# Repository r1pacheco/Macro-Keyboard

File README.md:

# Macro-Keyboard
Making a macro keyboard to increase efficiency in daily tasks and CAD/Programming hotkeys. 
Utilizes the *Black Pill V2.0* controller from *WeAct Studios* (STM32F411CEU6 package) controlled by the Arduino IDE.

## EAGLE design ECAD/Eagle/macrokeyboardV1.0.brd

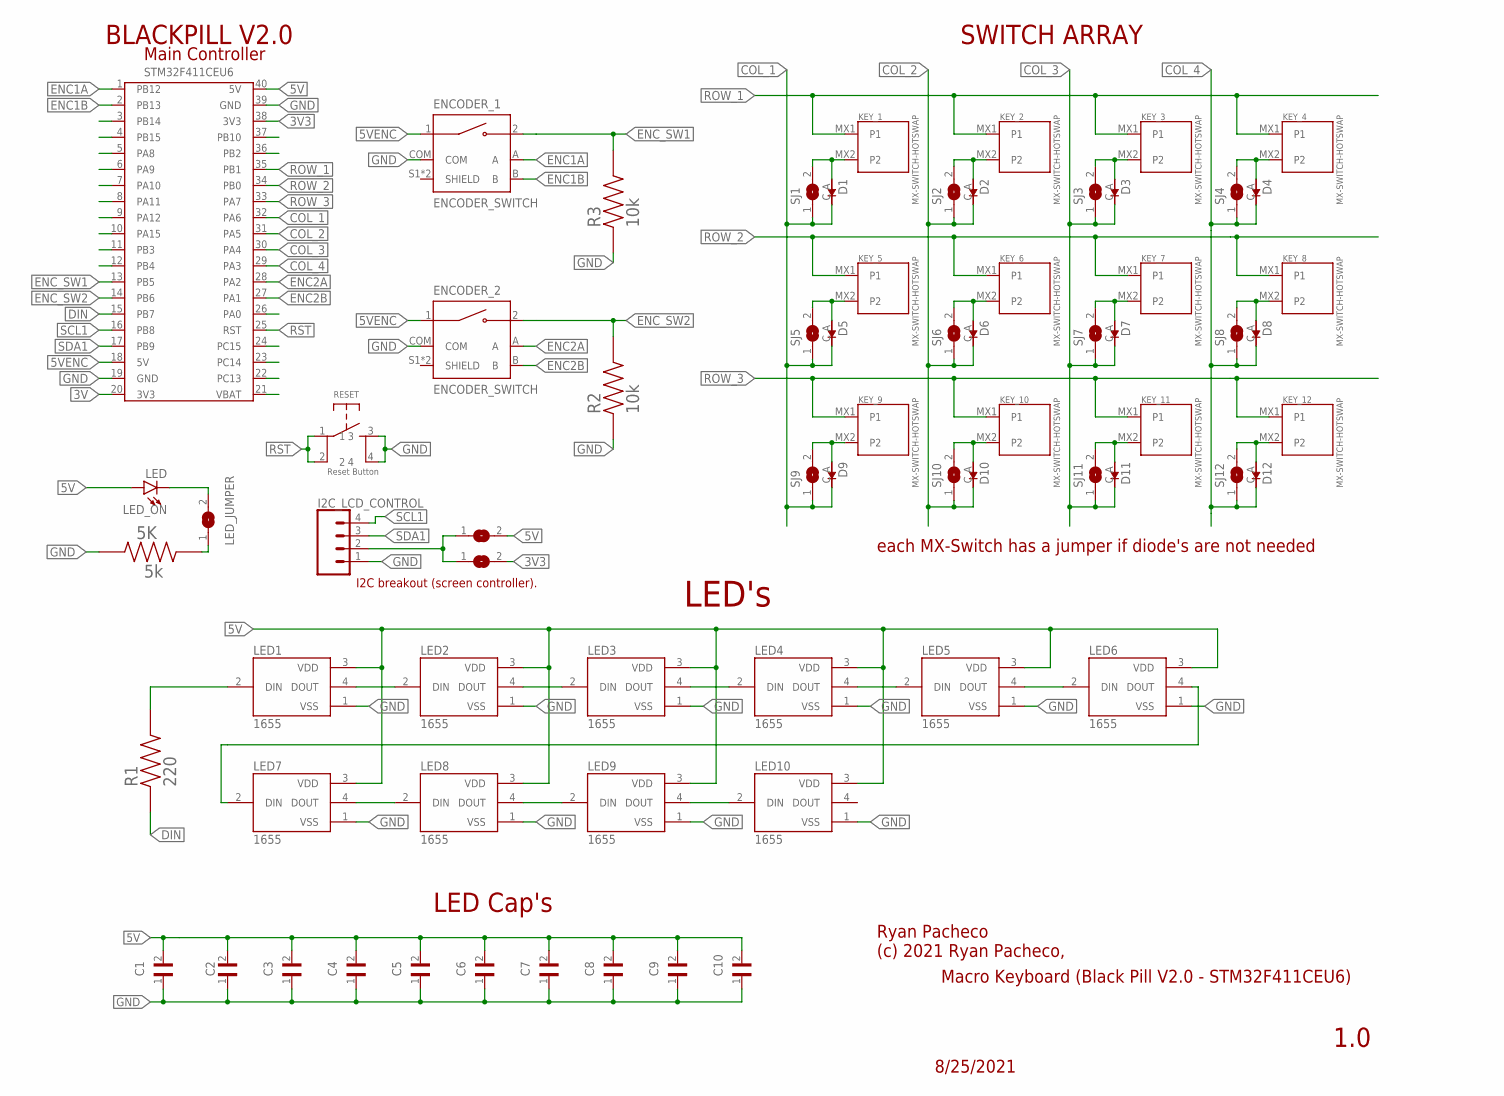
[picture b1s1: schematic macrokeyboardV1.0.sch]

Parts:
3.3V_I2C, 5V_I2C: SJ
5K: 5k; RESC3216X70N
C1: 100n; CAPC3216X88N
C2, C3, C4, C5, C7, C8, C9: C1206C104K5RAC7210; CAPC3216X88N
C6, C10: 100nF; CAPC3216X88N
D1, D2, D3, D4, D5, D6, D7, D8, D9, D10, D11, D12: 1N4148W-7-F; SOD3715X135N
ENCODER_1, ENCODER_2: ENCODER_SWITCH; XDCR_PEC11R-4215F-S0024
I2C_LCD_CONTROL: CONN_04; 1X04
KEY_1, KEY_2, KEY_3, KEY_4, KEY_5, KEY_6, KEY_7, KEY_8, KEY_9, KEY_10, KEY_11, KEY_12: MX-SWITCH-HOTSWAP; MXHSPCB-1U
LED1, LED2, LED3, LED4, LED5, LED6, LED7, LED8, LED9, LED10: 1655; LED_1655
LED_JUMPER: SJ
LED_ON: LED; LED-1206
R1: 220; RESC3216X70N
R2, R3: 10k; RESC3216X70N
RESET: Reset Button; PUSHBUTTON
SJ1, SJ2, SJ3, SJ4, SJ5, SJ6, SJ7, SJ8, SJ9, SJ10, SJ11, SJ12: SJ
U$2: STM32F411CEU6; BLACKPILL_V2

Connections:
3V: U$2.20 (3V3)
3V3: 3.3V_I2C.2, U$2.38 (3V3)
5V: 5V_I2C.2, C1.2, C2.2, C3.2, C4.2, C5.2, C6.2, C7.2, C8.2, C9.2, C10.2, LED1.3 (VDD), LED2.3 (VDD), LED3.3 (VDD), LED4.3 (VDD), LED5.3 (VDD), LED6.3 (VDD), LED7.3 (VDD), LED8.3 (VDD), LED9.3 (VDD), LED10.3 (VDD), LED_ON.A, U$2.40 (5V)
5VENC: ENCODER_1.1, ENCODER_2.1, U$2.18 (5V)
COL_1: D1.C (K), D5.C (K), D9.C (K), SJ1.1, SJ5.1, SJ9.1, U$2.32 (PA6)
COL_2: D2.C (K), D6.C (K), D10.C (K), SJ2.1, SJ6.1, SJ10.1, U$2.31 (PA5)
COL_3: D3.C (K), D7.C (K), D11.C (K), SJ3.1, SJ7.1, SJ11.1, U$2.30 (PA4)
COL_4: D4.C (K), D8.C (K), D12.C (K), SJ4.1, SJ8.1, SJ12.1, U$2.29 (PA3)
DIN: R1.1, U$2.15 (PB7)
ENC1A: ENCODER_1.A, U$2.1 (PB12)
ENC1B: ENCODER_1.B, U$2.2 (PB13)
ENC2A: ENCODER_2.A, U$2.28 (PA2)
ENC2B: ENCODER_2.B, U$2.27 (PA1)
ENC_SW1: ENCODER_1.2, R3.2, U$2.13 (PB5)
ENC_SW2: ENCODER_2.2, R2.2, U$2.14 (PB6)
GND: 5K.2, C1.1, C2.1, C3.1, C4.1, C5.1, C6.1, C7.1, C8.1, C9.1, C10.1, ENCODER_1.COM, ENCODER_2.COM, I2C_LCD_CONTROL.1, LED1.1 (VSS), LED2.1 (VSS), LED3.1 (VSS), LED4.1 (VSS), LED5.1 (VSS), LED6.1 (VSS), LED7.1 (VSS), LED8.1 (VSS), LED9.1 (VSS), LED10.1 (VSS), R2.1, R3.1, RESET.3, RESET.4, U$2.19 (GND), U$2.39 (GND)
unnamed: D1.A, KEY_1.MX2 (P2), SJ1.2
unnamed: D2.A, KEY_2.MX2 (P2), SJ2.2
unnamed: D3.A, KEY_3.MX2 (P2), SJ3.2
unnamed: D4.A, KEY_4.MX2 (P2), SJ4.2
unnamed: D5.A, KEY_5.MX2 (P2), SJ5.2
unnamed: D6.A, KEY_6.MX2 (P2), SJ6.2
unnamed: D7.A, KEY_7.MX2 (P2), SJ7.2
unnamed: D8.A, KEY_8.MX2 (P2), SJ8.2
unnamed: D9.A, KEY_9.MX2 (P2), SJ9.2
unnamed: D10.A, KEY_10.MX2 (P2), SJ10.2
unnamed: D11.A, KEY_11.MX2 (P2), SJ11.2
unnamed: D12.A, KEY_12.MX2 (P2), SJ12.2
unnamed: 5K.1, LED_JUMPER.1
unnamed: LED_JUMPER.2, LED_ON.C
unnamed: LED1.2 (DIN), R1.2
unnamed: LED1.4 (DOUT), LED2.2 (DIN)
unnamed: LED2.4 (DOUT), LED3.2 (DIN)
unnamed: LED7.4 (DOUT), LED8.2 (DIN)
unnamed: LED8.4 (DOUT), LED9.2 (DIN)
unnamed: 3.3V_I2C.1, 5V_I2C.1, I2C_LCD_CONTROL.2
unnamed: LED6.4 (DOUT), LED7.2 (DIN)
unnamed: LED9.4 (DOUT), LED10.2 (DIN)
unnamed: LED5.4 (DOUT), LED6.2 (DIN)
unnamed: LED4.4 (DOUT), LED5.2 (DIN)
unnamed: LED3.4 (DOUT), LED4.2 (DIN)
ROW_1: KEY_1.MX1 (P1), KEY_2.MX1 (P1), KEY_3.MX1 (P1), KEY_4.MX1 (P1), U$2.35 (PB1)
ROW_2: KEY_5.MX1 (P1), KEY_6.MX1 (P1), KEY_7.MX1 (P1), KEY_8.MX1 (P1), U$2.34 (PB0)
ROW_3: KEY_9.MX1 (P1), KEY_10.MX1 (P1), KEY_11.MX1 (P1), KEY_12.MX1 (P1), U$2.33 (PA7)
RST: RESET.1, RESET.2, U$2.25 (RST)
SCL1: I2C_LCD_CONTROL.4, U$2.16 (PB8)
SDA1: I2C_LCD_CONTROL.3, U$2.17 (PB9)

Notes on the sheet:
1.0
Macro Keyboard (Black Pill V2.0 - STM32F411CEU6)
8/25/2021
Ryan Pacheco (c) 2021 Ryan Pacheco,
SWITCH ARRAY
BLACKPILL V2.0
Main Controller
LED's
LED Cap's
each MX-Switch has a jumper if diode's are not needed
I2C breakout (screen controller).

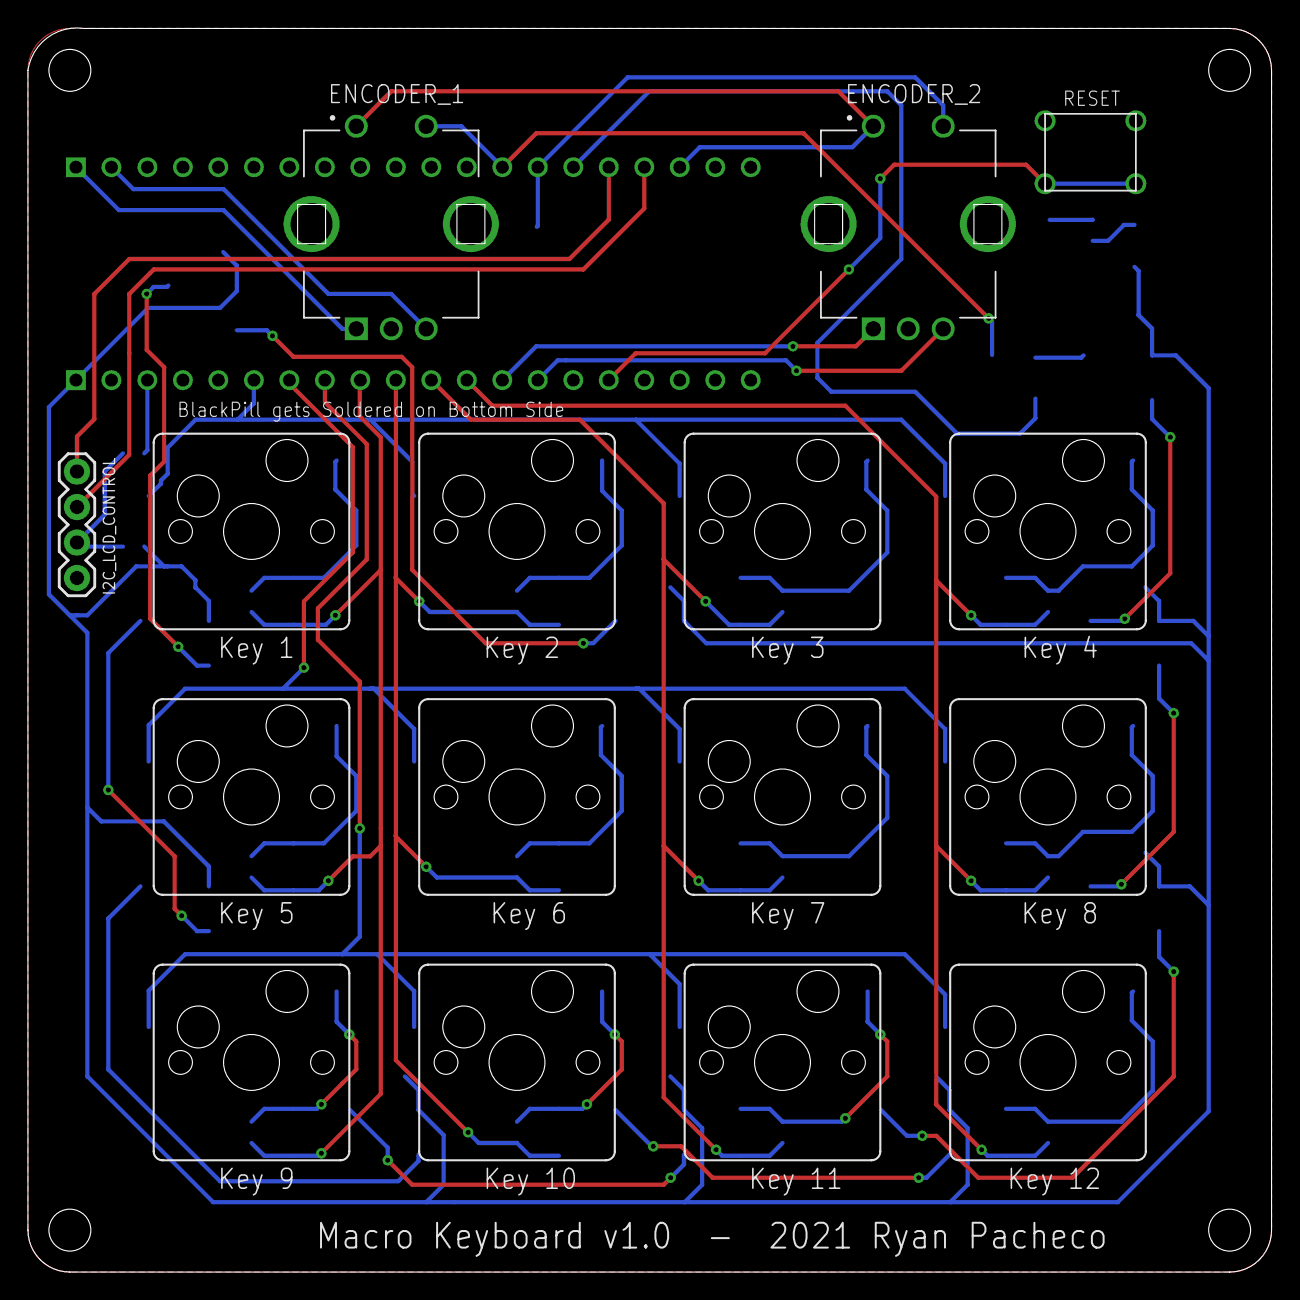
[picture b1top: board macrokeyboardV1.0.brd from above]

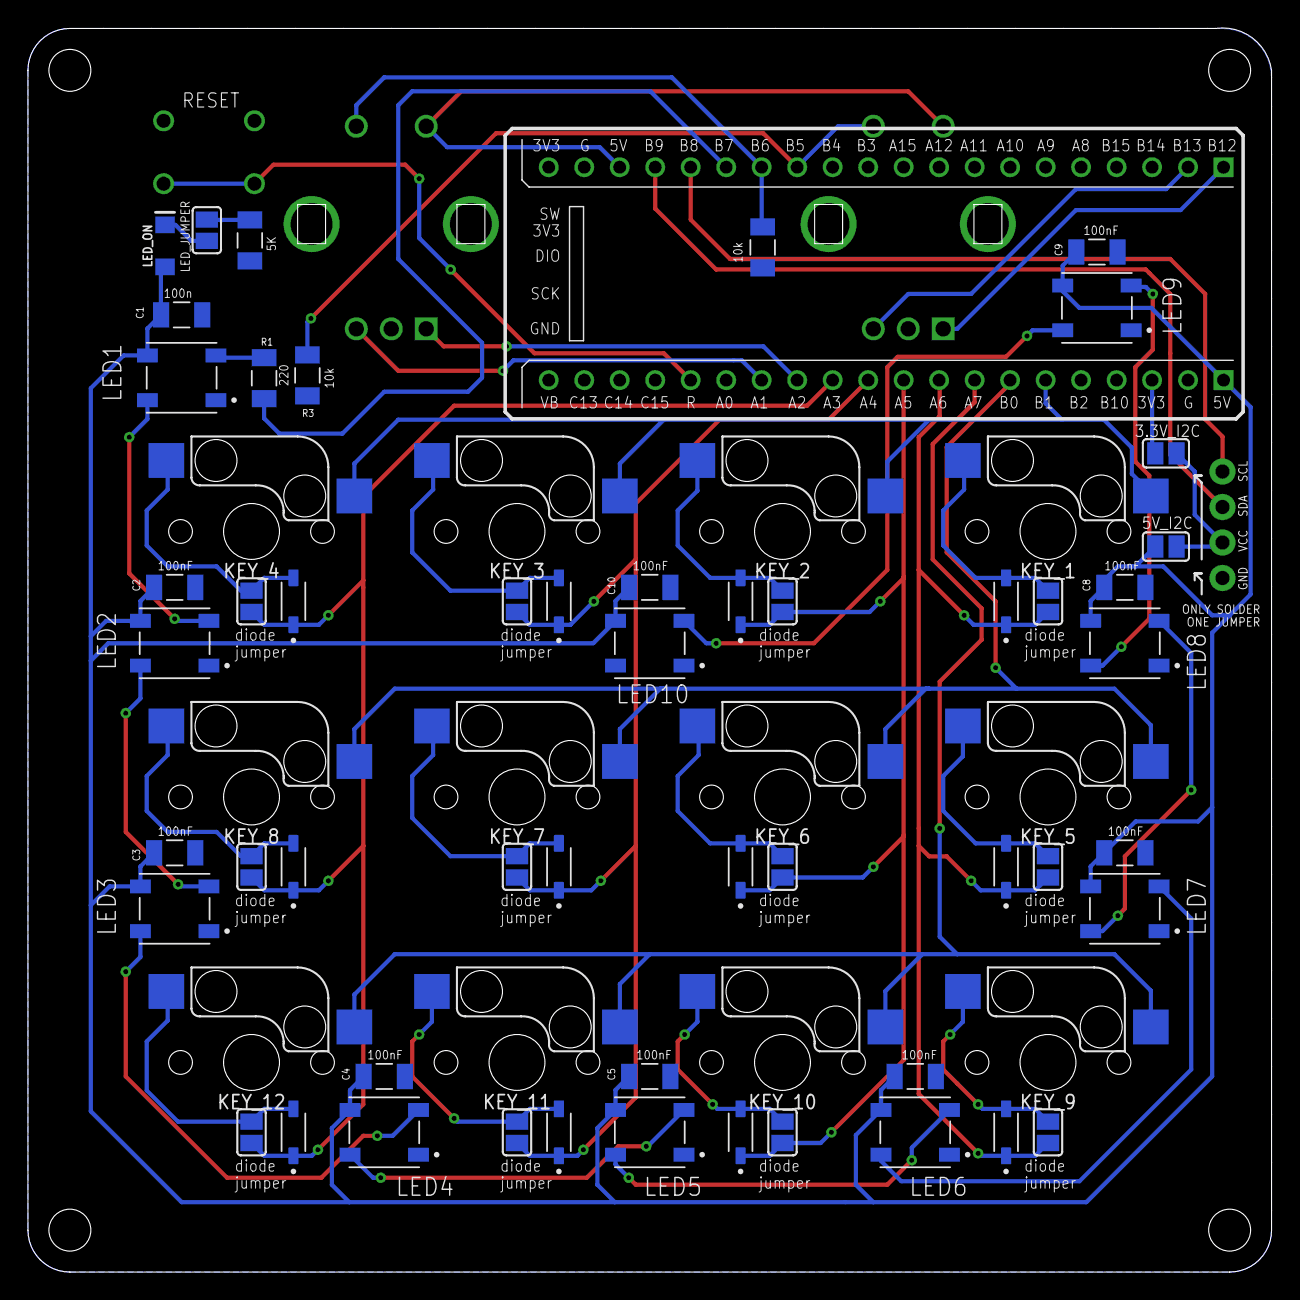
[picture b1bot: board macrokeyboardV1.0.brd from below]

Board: 2 copper layers, 89.0 x 89.0 mm, 69 parts (65 on the bottom side), 46 nets.

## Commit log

2021-08-14 Blackpill library for Eagle (Autodesk)
    No good libraries and footprints could be exported online, so I made my own with the proper specs and dimensions.
2021-09-30 adding all folders for first iteration. ECAD design, PCB Gerber's, case drawings, images, and BOM all added

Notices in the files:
parts and their libraries:
SparkFun-LED: Licensing: Creative Commons ShareAlike 4.0 International - https://creativecommons.org/licenses/by-sa/4.0
